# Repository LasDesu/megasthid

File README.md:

# MegaST HID adapter

Atari Mega ST adapter for input devices (keyboard, mouse, joysticks) based on ATmega168A. PS/2 interface is used to connect keyboard and mouse.

### WIP
Project is not complete yet, joysticks are not fully implemented.

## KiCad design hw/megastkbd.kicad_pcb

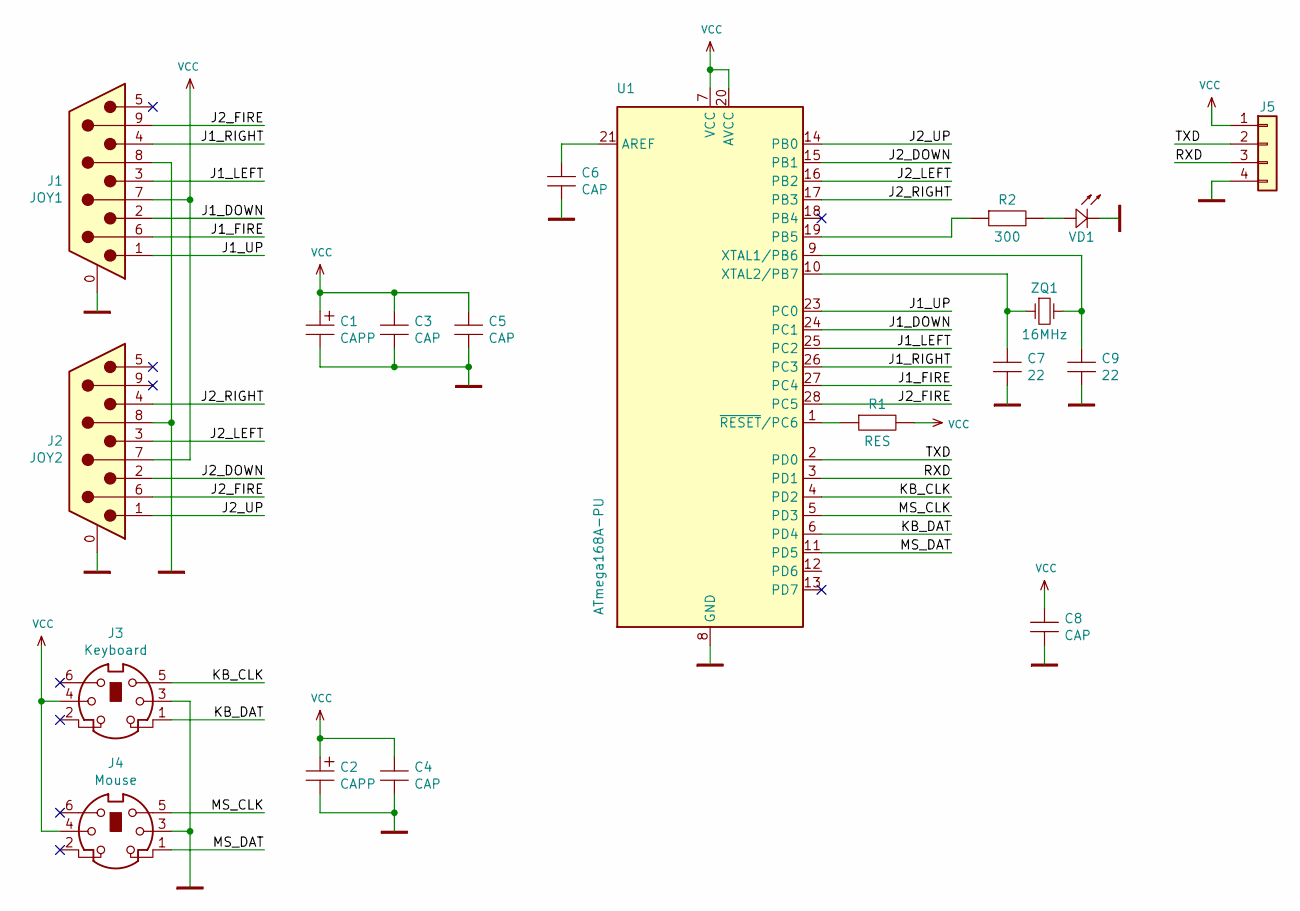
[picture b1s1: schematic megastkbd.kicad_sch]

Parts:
C1, C2: CAPP; CP_Radial_D5.0mm_P2.50mm
C3, C5, C6: CAP; C_0805_2012Metric_Pad1.18x1.45mm_HandSolder
C4, C8: CAP; C_Disc_D7.5mm_W2.5mm_P5.00mm
C7, C9: 22; C_0805_2012Metric_Pad1.18x1.45mm_HandSolder
J1: JOY1; DSUB-9_Male_Horizontal_P2.77x2.84mm_EdgePinOffset4.94mm_Hou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
J2: JOY2; DSUB-9_Male_Horizontal_P2.77x2.84mm_EdgePinOffset4.94mm_Hou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
J3: Keyboard; Mini_din6
J4: Mouse; Mini_din6
J5: Conn_01x04; JST_EH_B4B-EH-A_1x04_P2.50mm_Vertical
R1: RES; R_0805_2012Metric_Pad1.20x1.40mm_HandSolder
R2: 300; R_0805_2012Metric_Pad1.20x1.40mm_HandSolder
U1: ATmega168A-PU; DIP-28_W7.62mm_Socket
VD1: LED; LED_D5.0mm
ZQ1: 16MHz; Crystal_HC49-4H_Vertical

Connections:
/J1_DOWN: J1.2, U1.24 (PC1)
/J1_FIRE: J1.6, U1.27 (PC4)
/J1_LEFT: J1.3, U1.25 (PC2)
/J1_RIGHT: J1.4, U1.26 (PC3)
/J1_UP: J1.1, U1.23 (PC0)
/J2_DOWN: J2.2, U1.15 (PB1)
/J2_FIRE: J1.9, J2.6, U1.28 (PC5)
/J2_LEFT: J2.3, U1.16 (PB2)
/J2_RIGHT: J2.4, U1.17 (PB3)
/J2_UP: J2.1, U1.14 (PB0)
/KB_CLK: J3.5, U1.4 (PD2)
/KB_DAT: J3.1, U1.6 (PD4)
/MS_CLK: J4.5, U1.5 (PD3)
/MS_DAT: J4.1, U1.11 (PD5)
/RXD: J5.3, U1.3 (PD1)
/TXD: J5.2, U1.2 (PD0)
GND: C1.2, C2.2, C3.2, C4.2, C5.2, C6.2, C7.2, C8.2, C9.2, J1.0 (PAD), J1.8, J2.0 (PAD), J2.8, J3.3, J4.3, J5.4, U1.8 (GND), U1.22 (GND), VD1.1
unnamed: C6.1, U1.21 (AREF)
unnamed: C7.1, U1.10 (XTAL2/PB7), ZQ1.1
unnamed: C9.1, U1.9 (XTAL1/PB6), ZQ1.2
unnamed: R1.1, U1.1 (~RESET/PC6)
unnamed: R2.1, U1.19 (PB5)
unnamed: R2.2, VD1.2
VCC: C1.1, C2.1, C3.1, C4.1, C5.1, C8.1, J1.7, J2.7, J3.4, J4.4, J5.1, R1.2, U1.7 (VCC), U1.20 (AVCC)

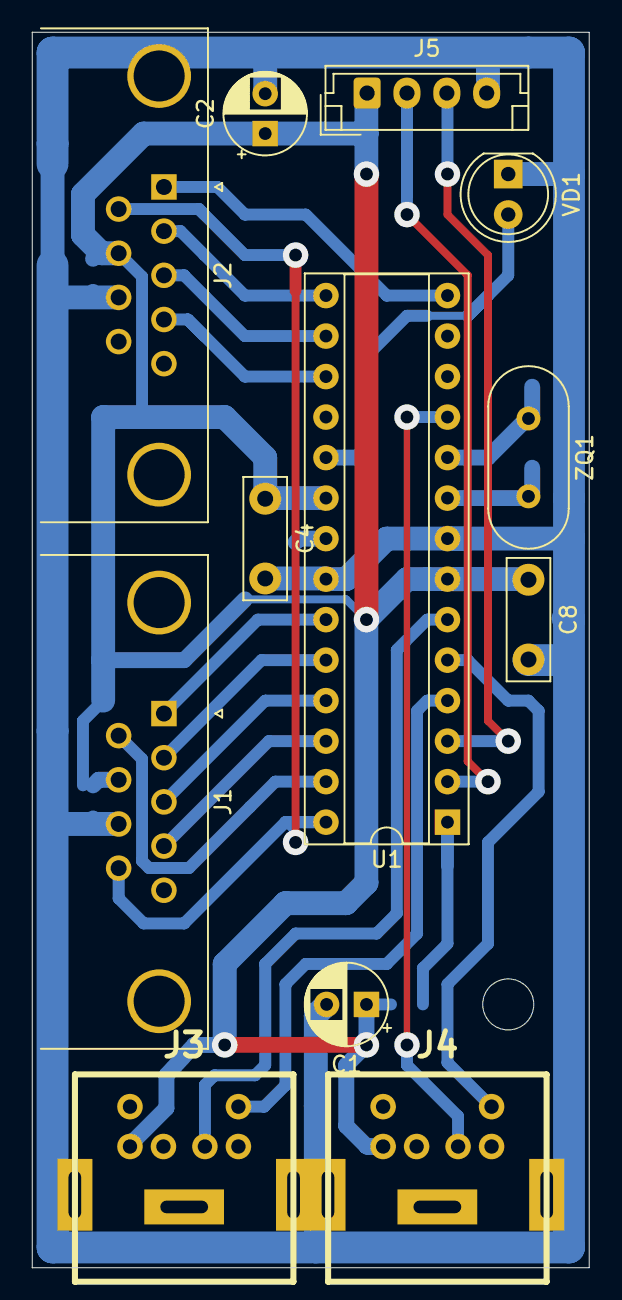
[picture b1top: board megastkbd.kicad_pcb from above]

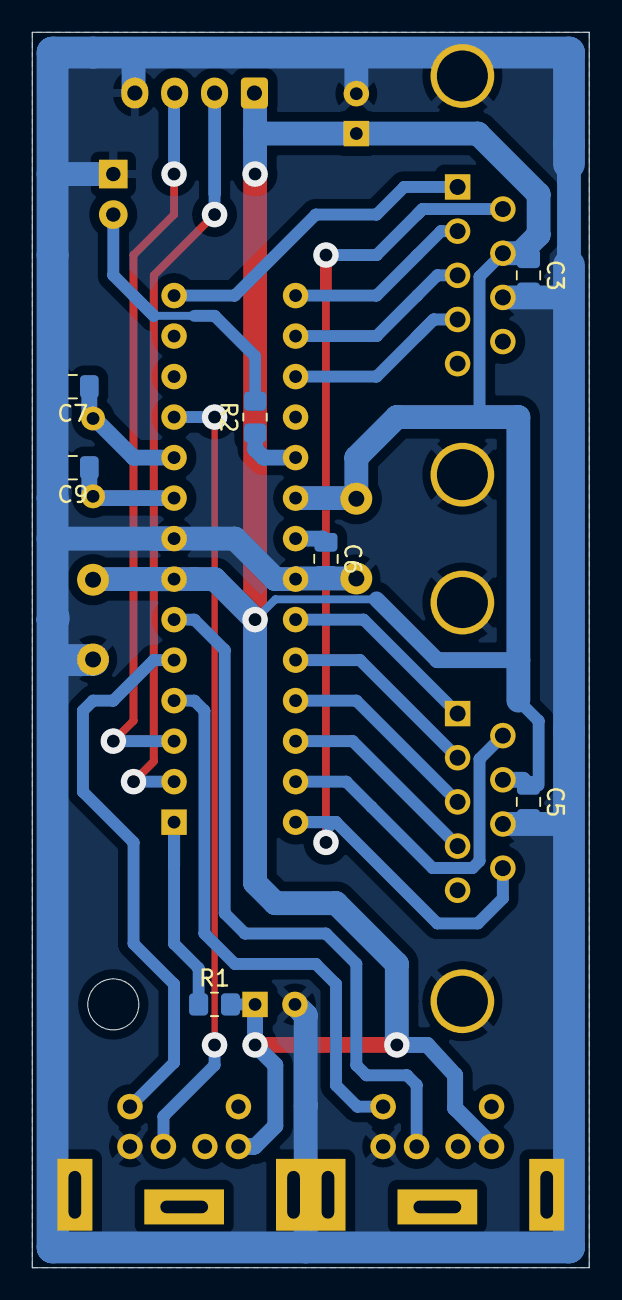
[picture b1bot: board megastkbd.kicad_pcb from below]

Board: 2 copper layers, 34.9 x 77.5 mm, 19 parts (7 on the bottom side), 24 nets.

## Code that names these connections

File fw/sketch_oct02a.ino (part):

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#define J0_RIGHT	A3
#define J0_FIRE		A4

#define J1_UP		8
#define J1_DOWN		9
#define J1_LEFT		10
#define J1_RIGHT	11
#define J1_FIRE		A5

static inline void ikbd_send( uint8_t val )
{
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	pinMode( J0_LEFT, INPUT_PULLUP );
	pinMode( J0_RIGHT, INPUT_PULLUP );

	pinMode( J1_FIRE, INPUT_PULLUP );
	pinMode( J1_UP, INPUT_PULLUP );
	pinMode( J1_DOWN, INPUT_PULLUP );
	pinMode( J1_LEFT, INPUT_PULLUP );
	pinMode( J1_RIGHT, INPUT_PULLUP );

	mouse_phase = -1;
	ikbd_pause = 0;
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
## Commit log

2024-09-27 Initial commit, joystick support not fully implemented

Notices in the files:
fw/sketch_oct02a.ino:
fuck you, MCb, and fuck your GPL
and GPL is just pure evil virus
